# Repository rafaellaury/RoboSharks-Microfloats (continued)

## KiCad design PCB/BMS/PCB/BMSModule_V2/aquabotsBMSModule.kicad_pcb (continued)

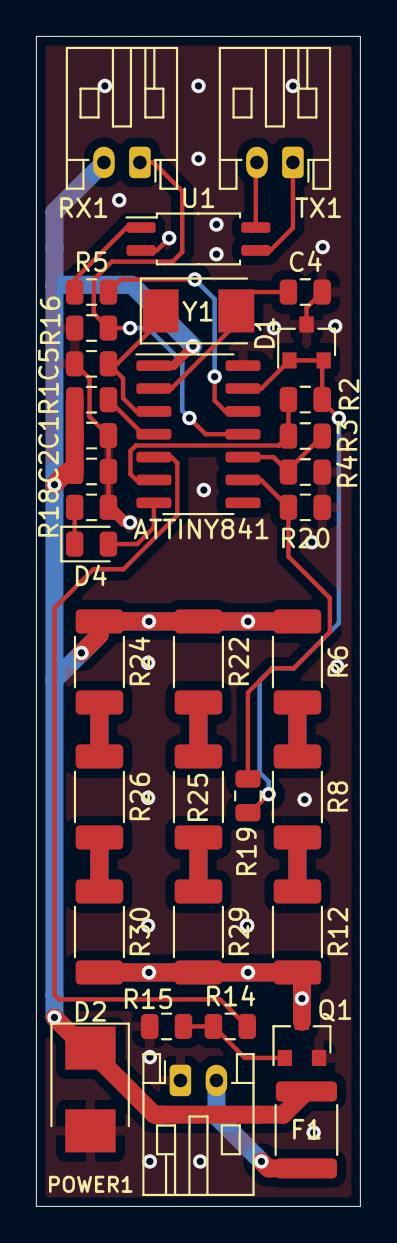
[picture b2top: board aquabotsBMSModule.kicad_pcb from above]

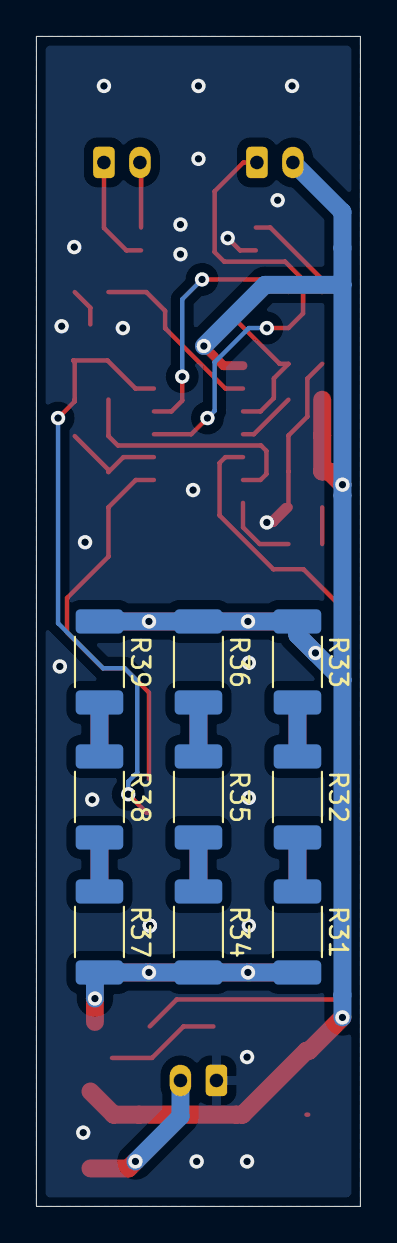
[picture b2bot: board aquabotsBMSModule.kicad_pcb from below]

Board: 2 copper layers, 18.0 x 65.0 mm, 44 parts (9 on the bottom side), 32 nets.

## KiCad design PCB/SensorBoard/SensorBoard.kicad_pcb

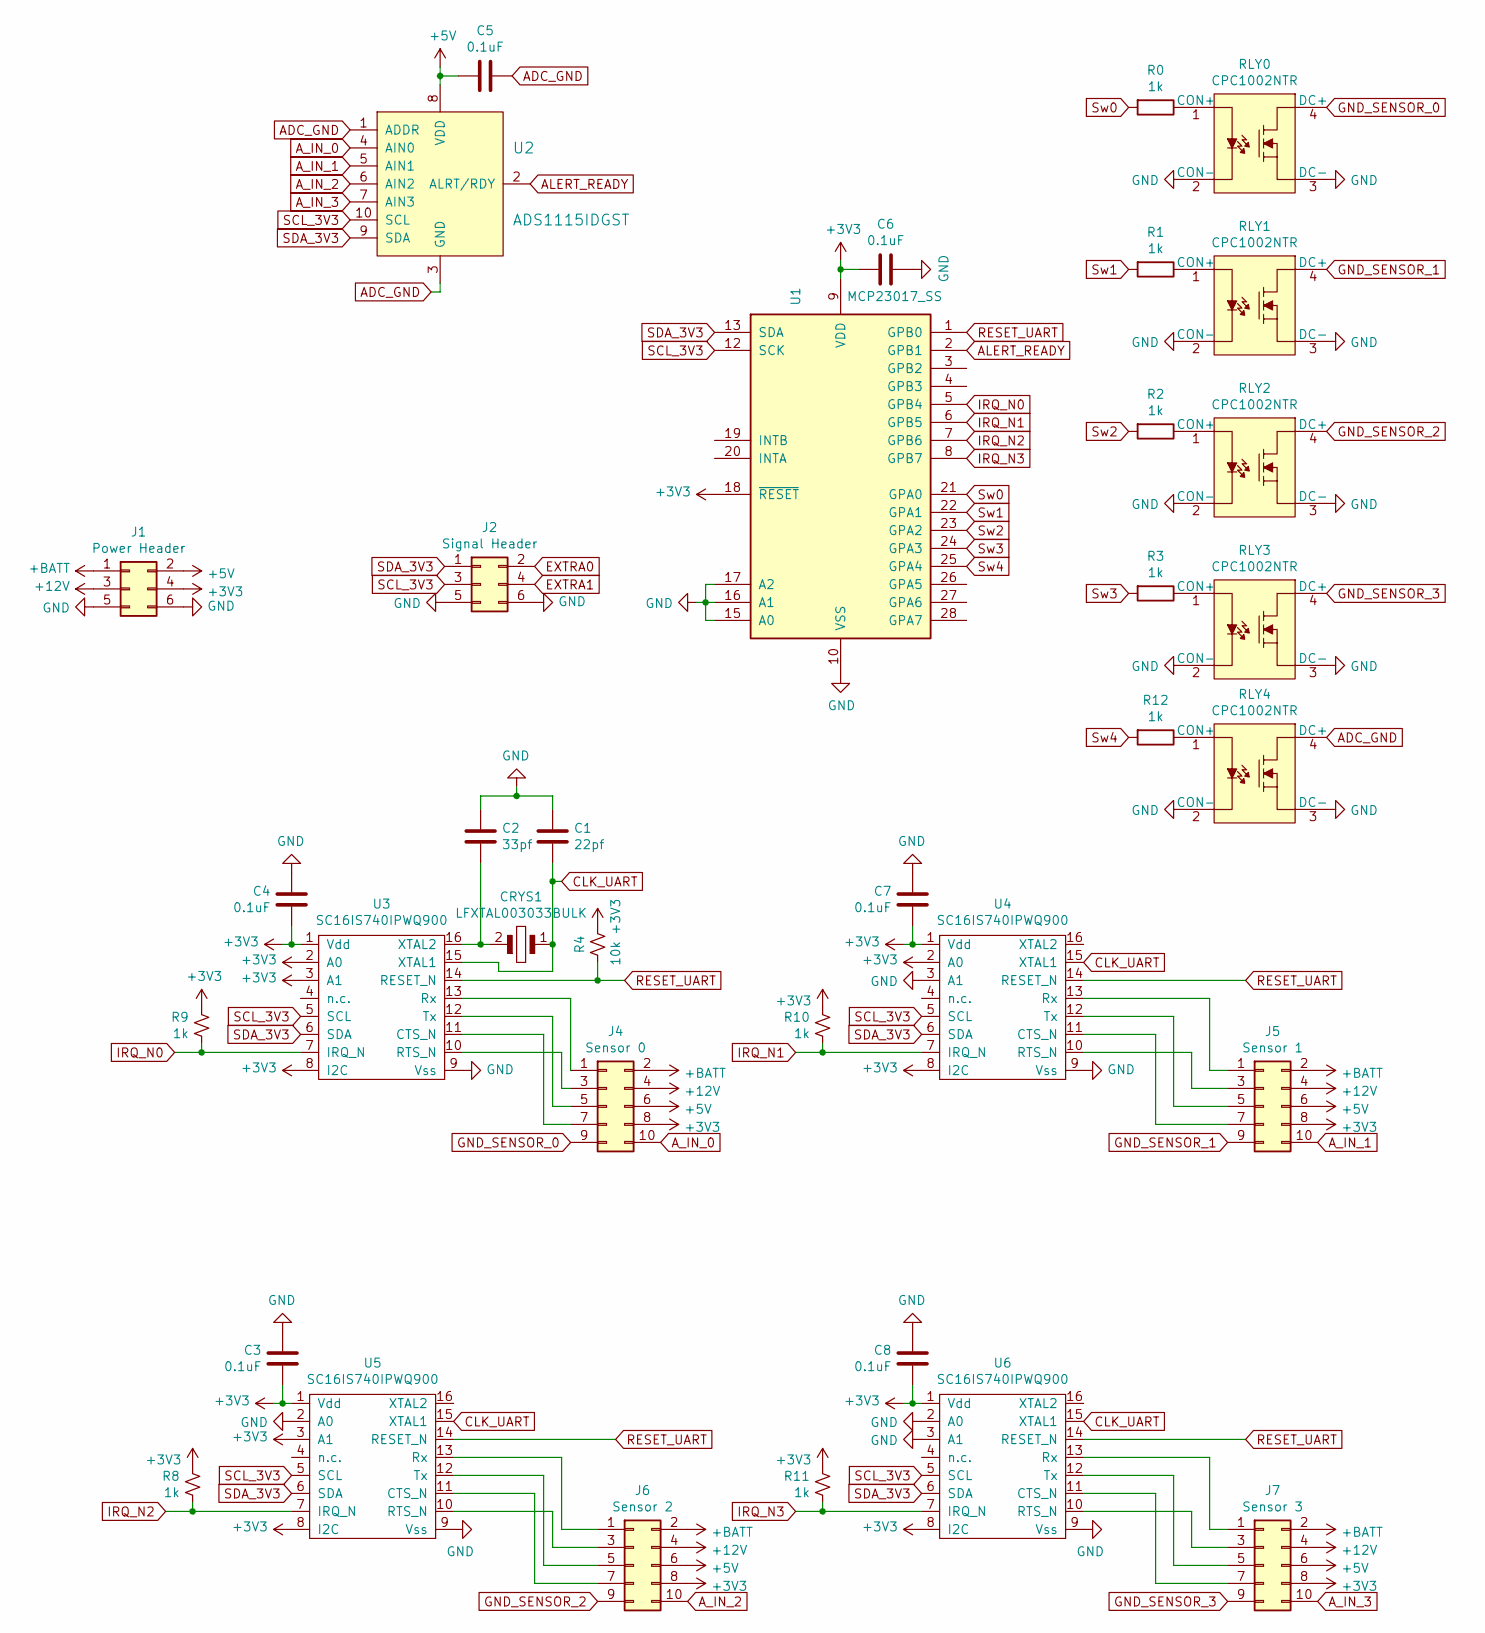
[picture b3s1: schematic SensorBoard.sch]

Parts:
C1: 22pf; C_0603_1608Metric_Pad1.05x0.95mm_HandSolder
C2: 33pf; C_0603_1608Metric_Pad1.05x0.95mm_HandSolder
C3, C4, C5, C6, C7, C8: 0.1uF; C_0603_1608Metric_Pad1.05x0.95mm_HandSolder
CRYS1: LFXTAL003033BULK; Crystal_HC49-U_Vertical
J1: Power Header; PinHeader_2x03_P2.54mm_Vertical
J2: Signal Header; PinHeader_2x03_P2.54mm_Vertical
J4: Sensor 0; Molex_Nano-Fit_105314-xx10_2x05_P2.50mm_Horizontal
J5: Sensor 1; Molex_Nano-Fit_105314-xx10_2x05_P2.50mm_Horizontal
J6: Sensor 2; Molex_Nano-Fit_105314-xx10_2x05_P2.50mm_Horizontal
J7: Sensor 3; Molex_Nano-Fit_105314-xx10_2x05_P2.50mm_Horizontal
R0, R1, R2, R3, R8, R9, R10, R11, R12: 1k; R_0805_2012Metric_Pad1.15x1.40mm_HandSolder
R4: 10k; R_0805_2012Metric_Pad1.15x1.40mm_HandSolder
RLY0, RLY1, RLY2, RLY3, RLY4: CPC1002NTR; SOP-4_3.8x4.1mm_P2.54mm; MPN CPC1002NTR; Digi-Key_PN CLA230CT-ND
U1: MCP23017_SS; SSOP-28_5.3x10.2mm_P0.65mm
U2: ADS1115IDGST; VSSOP-10_3x3mm_P0.5mm; MPN ADS1115IDGST; Digi-Key_PN 296-24934-1-ND
U3, U4, U5, U6: SC16IS740IPWQ900; TSSOP-16_4.4x5mm_P0.65mm

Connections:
+3V3: C3.2, C4.2, C6.2, C7.2, C8.2, J1.4, J4.8, J5.8, J6.8, J7.8, R4.2, R8.2, R9.2, R10.2, R11.2, U1.9 (VDD), U1.18 (~RESET~), U3.1 (Vdd), U3.2 (A0), U3.3 (A1), U3.8 (I2C), U4.1 (Vdd), U4.2 (A0), U4.8 (I2C), U5.1 (Vdd), U5.3 (A1), U5.8 (I2C), U6.1 (Vdd), U6.8 (I2C)
+5V: C5.2, J1.2, J4.6, J5.6, J6.6, J7.6, U2.8 (VDD)
+12V: J1.3, J4.4, J5.4, J6.4, J7.4
+BATT: J1.1, J4.2, J5.2, J6.2, J7.2
ADC_GND: C5.1, RLY4.4 (DC+), U2.1 (ADDR), U2.3 (GND)
ALERT_READY: U1.2 (GPB1), U2.2 (ALRT/RDY)
A_IN_0: J4.10, U2.4 (AIN0)
A_IN_1: J5.10, U2.5 (AIN1)
A_IN_2: J6.10, U2.6 (AIN2)
A_IN_3: J7.10, U2.7 (AIN3)
CLK_UART: C1.2, CRYS1.1, U3.15 (XTAL1), U4.15 (XTAL1), U5.15 (XTAL1), U6.15 (XTAL1)
EXTRA0: J2.2
EXTRA1: J2.4
GND: C1.1, C2.1, C3.1, C4.1, C6.1, C7.1, C8.1, J1.5, J1.6, J2.5, J2.6, RLY0.2 (CON-), RLY0.3 (DC-), RLY1.2 (CON-), RLY1.3 (DC-), RLY2.2 (CON-), RLY2.3 (DC-), RLY3.2 (CON-), RLY3.3 (DC-), RLY4.2 (CON-), RLY4.3 (DC-), U1.10 (VSS), U1.15 (A0), U1.16 (A1), U1.17 (A2), U3.9 (Vss), U4.3 (A1), U4.9 (Vss), U5.2 (A0), U5.9 (Vss), U6.2 (A0), U6.3 (A1), U6.9 (Vss)
GND_SENSOR_0: J4.9, RLY0.4 (DC+)
GND_SENSOR_1: J5.9, RLY1.4 (DC+)
GND_SENSOR_2: J6.9, RLY2.4 (DC+)
GND_SENSOR_3: J7.9, RLY3.4 (DC+)
IRQ_N0: R9.1, U1.5 (GPB4), U3.7 (IRQ_N)
IRQ_N1: R10.1, U1.6 (GPB5), U4.7 (IRQ_N)
IRQ_N2: R8.1, U1.7 (GPB6), U5.7 (IRQ_N)
IRQ_N3: R11.1, U1.8 (GPB7), U6.7 (IRQ_N)
unnamed: C2.2, CRYS1.2, U3.16 (XTAL2)
unnamed: J4.1, U3.13 (Rx)
unnamed: J4.3, U3.10 (RTS_N)
unnamed: J4.5, U3.12 (Tx)
unnamed: J4.7, U3.11 (CTS_N)
unnamed: J5.1, U4.13 (Rx)
unnamed: J5.3, U4.10 (RTS_N)
unnamed: J5.5, U4.12 (Tx)
unnamed: J5.7, U4.11 (CTS_N)
unnamed: J6.1, U5.13 (Rx)
unnamed: J6.3, U5.10 (RTS_N)
unnamed: J6.5, U5.12 (Tx)
unnamed: J6.7, U5.11 (CTS_N)
unnamed: J7.1, U6.13 (Rx)
unnamed: J7.3, U6.10 (RTS_N)
unnamed: J7.5, U6.12 (Tx)
unnamed: J7.7, U6.11 (CTS_N)
unnamed: R0.1, RLY0.1 (CON+)
unnamed: R1.1, RLY1.1 (CON+)
unnamed: R2.1, RLY2.1 (CON+)
unnamed: R3.1, RLY3.1 (CON+)
unnamed: R12.1, RLY4.1 (CON+)
RESET_UART: R4.1, U1.1 (GPB0), U3.14 (RESET_N), U4.14 (RESET_N), U5.14 (RESET_N), U6.14 (RESET_N)
SCL_3V3: J2.3, U1.12 (SCK), U2.10 (SCL), U3.5 (SCL), U4.5 (SCL), U5.5 (SCL), U6.5 (SCL)
SDA_3V3: J2.1, U1.13 (SDA), U2.9 (SDA), U3.6 (SDA), U4.6 (SDA), U5.6 (SDA), U6.6 (SDA)
Sw0: R0.2, U1.21 (GPA0)
Sw1: R1.2, U1.22 (GPA1)
Sw2: R2.2, U1.23 (GPA2)
Sw3: R3.2, U1.24 (GPA3)
Sw4: R12.2, U1.25 (GPA4)

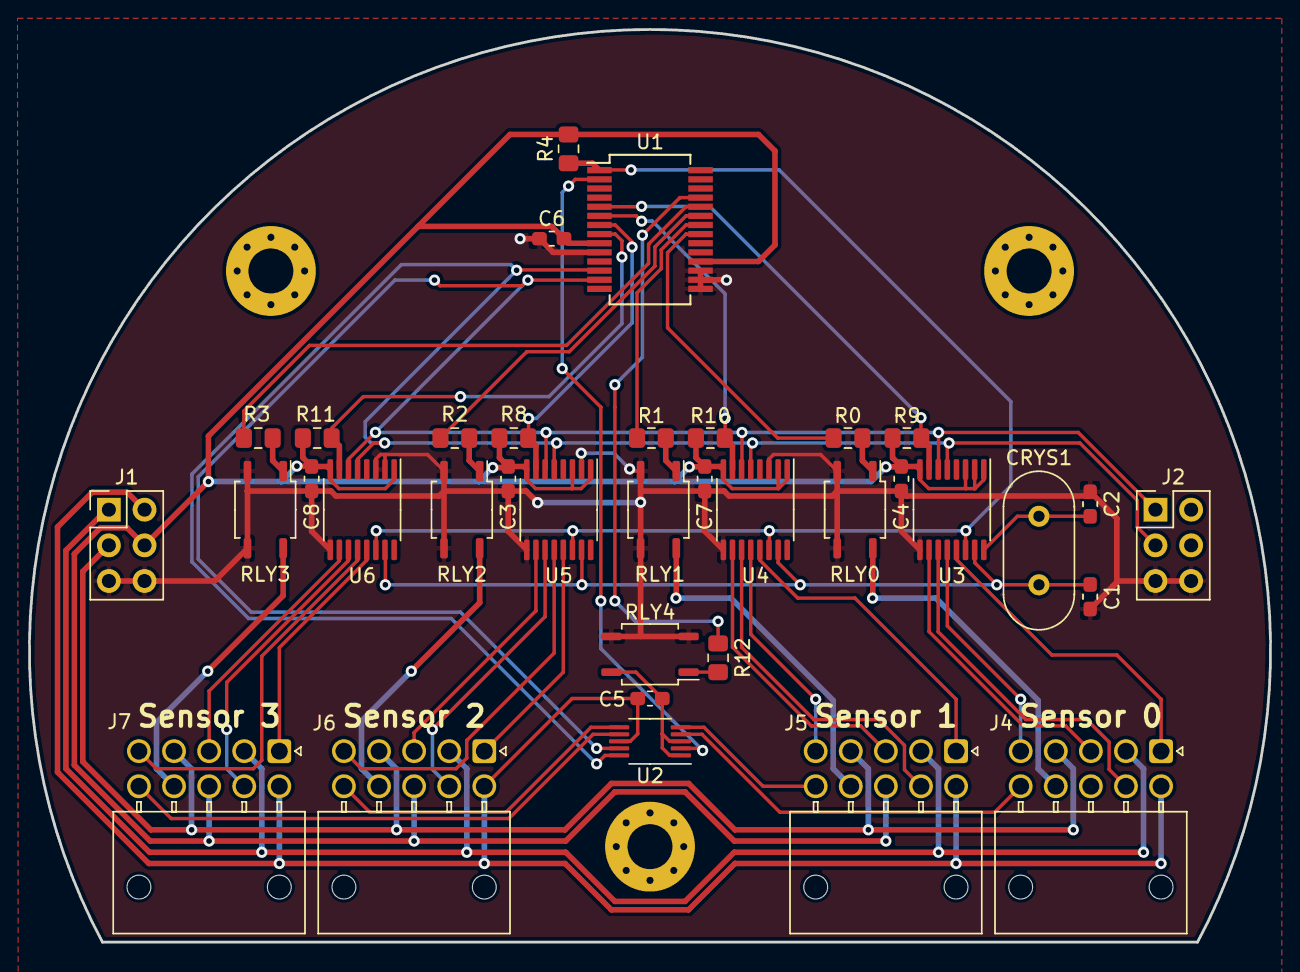
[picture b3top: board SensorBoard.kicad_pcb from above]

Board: 2 copper layers, 88.4 x 65.0 mm, 36 parts (0 on the bottom side), 50 nets.

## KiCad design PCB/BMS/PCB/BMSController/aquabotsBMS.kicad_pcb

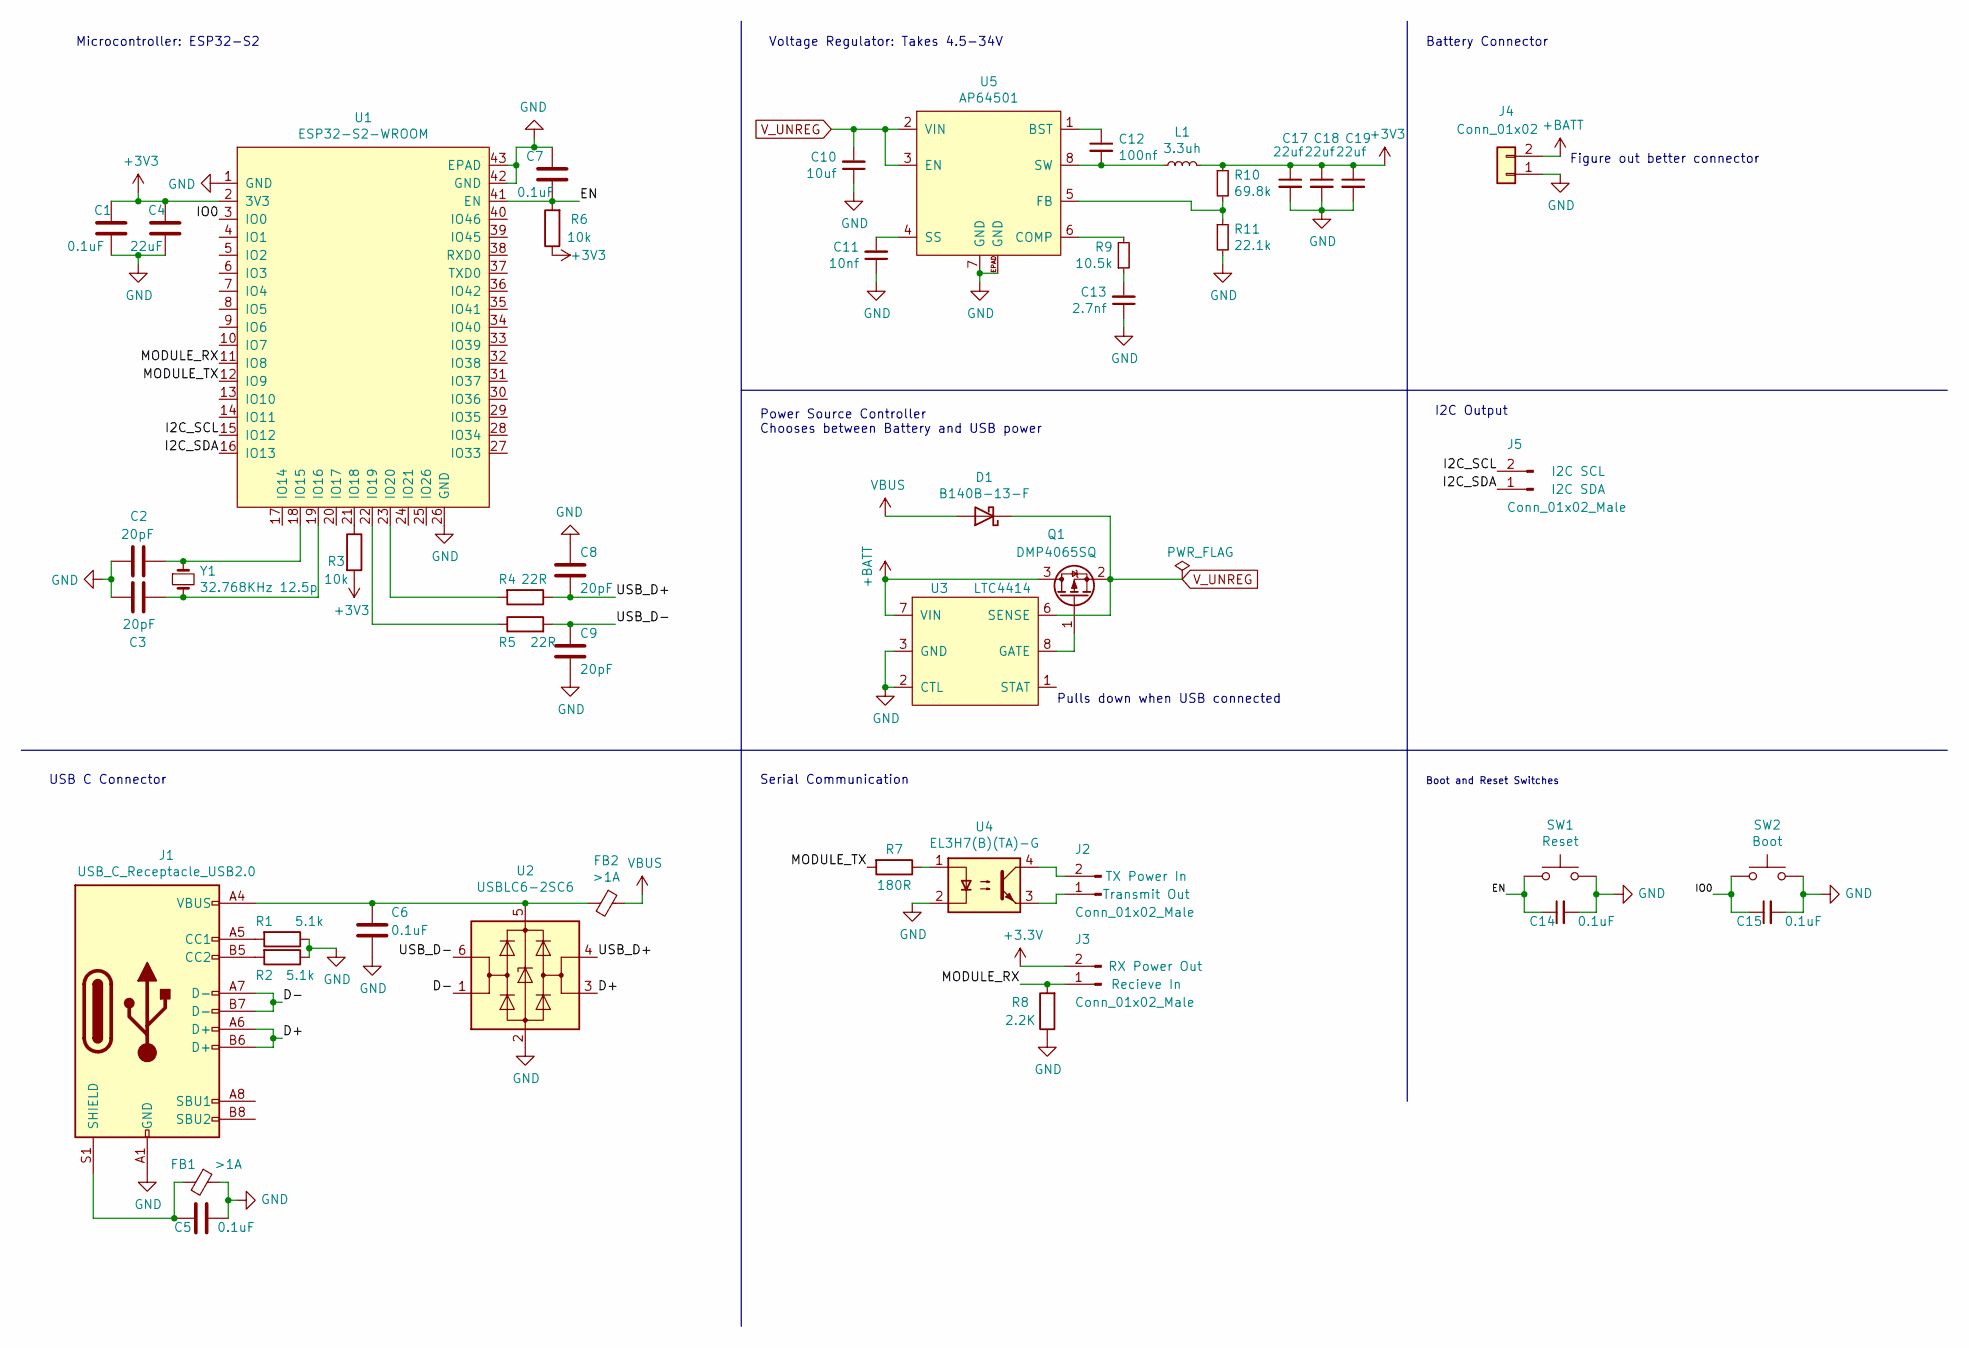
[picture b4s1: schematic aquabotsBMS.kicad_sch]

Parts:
C1, C5, C6, C7, C14, C15: 0.1uF; C_0603_1608Metric
C2, C3, C8, C9: 20pF; C_0603_1608Metric
C4: 22uF; C_0603_1608Metric
C10: 10uf; C_1206_3216Metric
C11: 10nf; C_0603_1608Metric
C12: 100nf; C_0603_1608Metric
C13: 2.7nf; C_0603_1608Metric
C17, C18, C19: 22uf; C_1206_3216Metric
D1: B140B-13-F; D_SMA
FB1, FB2: >1A; L_0603_1608Metric
J1: USB_C_Receptacle_USB2.0; USB_C_Receptacle_HRO_TYPE-C-31-M-12
J2, J3, J5: Conn_01x02_Male; JST_PH_S2B-PH-K_1x02_P2.00mm_Horizontal
J4: Conn_01x02; PinHeader_1x02_P2.54mm_Vertical
L1: 3.3uh; L_Wuerth_HCI-1050
Q1: DMP4065SQ; SOT-23
R1, R2: 5.1k; R_0603_1608Metric
R3, R6: 10k; R_0603_1608Metric
R4, R5: 22R; R_0603_1608Metric
R7: 180R; R_0603_1608Metric
R8: 2.2K; R_0603_1608Metric; LCSCStockCode C17520
R9: 10.5k; R_0603_1608Metric
R10: 69.8k; R_0603_1608Metric
R11: 22.1k; R_0603_1608Metric
SW1: Reset; SW_Push_SPST_NO_Alps_SKRK
SW2: Boot; SW_Push_SPST_NO_Alps_SKRK
U1: ESP32-S2-WROOM
U2: USBLC6-2SC6; SOT-23-6
U3: LTC4414; MSOP-8_3x3mm_P0.65mm
U4: EL3H7(B)(TA)-G; SOP-4_4.4x2.6mm_P1.27mm; LCSCStockCode C32565
U5: AP64501; AP64501SP-13
Y1: 32.768KHz 12.5p; Crystal_SMD_3215-2Pin_3.2x1.5mm

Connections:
+BATT: J4.2, Q1.3 (D), U3.7 (VIN)
/D+: J1.A6 (D+), J1.B6 (D+), U2.3 (I/O2)
/D-: J1.A7 (D-), J1.B7 (D-), U2.1 (I/O1)
/EN: C7.2, C14.1, R6.2, SW1.1, U1.41 (EN)
/I2C_SCL: J5.2, U1.15 (IO12)
/I2C_SDA: J5.1, U1.16 (IO13)
/IO0: C15.1, SW2.1, U1.3 (IO0)
/MODULE_RX: J3.1, R8.2, U1.11 (IO8)
/MODULE_TX: R7.2, U1.12 (IO9)
/USB_D+: C8.2, R4.1, U2.4 (I/O2)
/USB_D-: C9.1, R5.2, U2.6 (I/O1)
GND: C1.2, C2.2, C3.1, C4.2, C5.2, C6.2, C7.1, C8.1, C9.2, C10.1, C11.1, C13.1, C14.2, C15.2, C17.2, C18.2, C19.2, FB1.1, J1.A1 (GND), J1.A12 (GND), J1.B1 (GND), J1.B12 (GND), J4.1, R1.1, R2.1, R8.1, R11.2, SW1.2, SW2.2, U1.1 (GND), U1.26 (GND), U1.42 (GND), U1.43 (EPAD), U2.2 (GND), U3.2 (CTL), U3.3 (GND), U4.2, U5.7 (GND), U5.EPAD (GND)
unnamed: C2.1, U1.18 (IO15), Y1.1
unnamed: C3.2, U1.19 (IO16), Y1.2
unnamed: C5.1, FB1.2, J1.S1 (SHIELD)
unnamed: C6.1, FB2.2, J1.A4 (VBUS), J1.A9 (VBUS), J1.B4 (VBUS), J1.B9 (VBUS), U2.5 (VBUS)
unnamed: C11.2, U5.4 (SS)
unnamed: C12.1, U5.1 (BST)
unnamed: C12.2, L1.1, U5.8 (SW)
unnamed: C13.2, R9.1
unnamed: J1.A5 (CC1), R1.2
unnamed: J1.B5 (CC2), R2.2
unnamed: J2.1, U4.3
unnamed: J2.2, U4.4
unnamed: Q1.1 (G), U3.8 (GATE)
unnamed: R3.1, U1.21 (IO18)
unnamed: R4.2, U1.23 (IO20)
unnamed: R5.1, U1.22 (IO19)
unnamed: R7.1, U4.1
unnamed: R9.2, U5.6 (COMP)
unnamed: R10.2, R11.1, U5.5 (FB)
VBUS: D1.2 (A), FB2.1
V_UNREG: C10.2, D1.1 (K), Q1.2 (S), U3.6 (SENSE), U5.2 (VIN), U5.3 (EN)

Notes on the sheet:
Figure out better connector
I2C Output
Pulls down when USB connected
Serial Communication
Microcontroller: ESP32-S2
Power Source Controller Chooses between Battery and USB power
Voltage Regulator: Takes 4.5-34V
Battery Connector
Boot and Reset Switches
USB C Connector

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
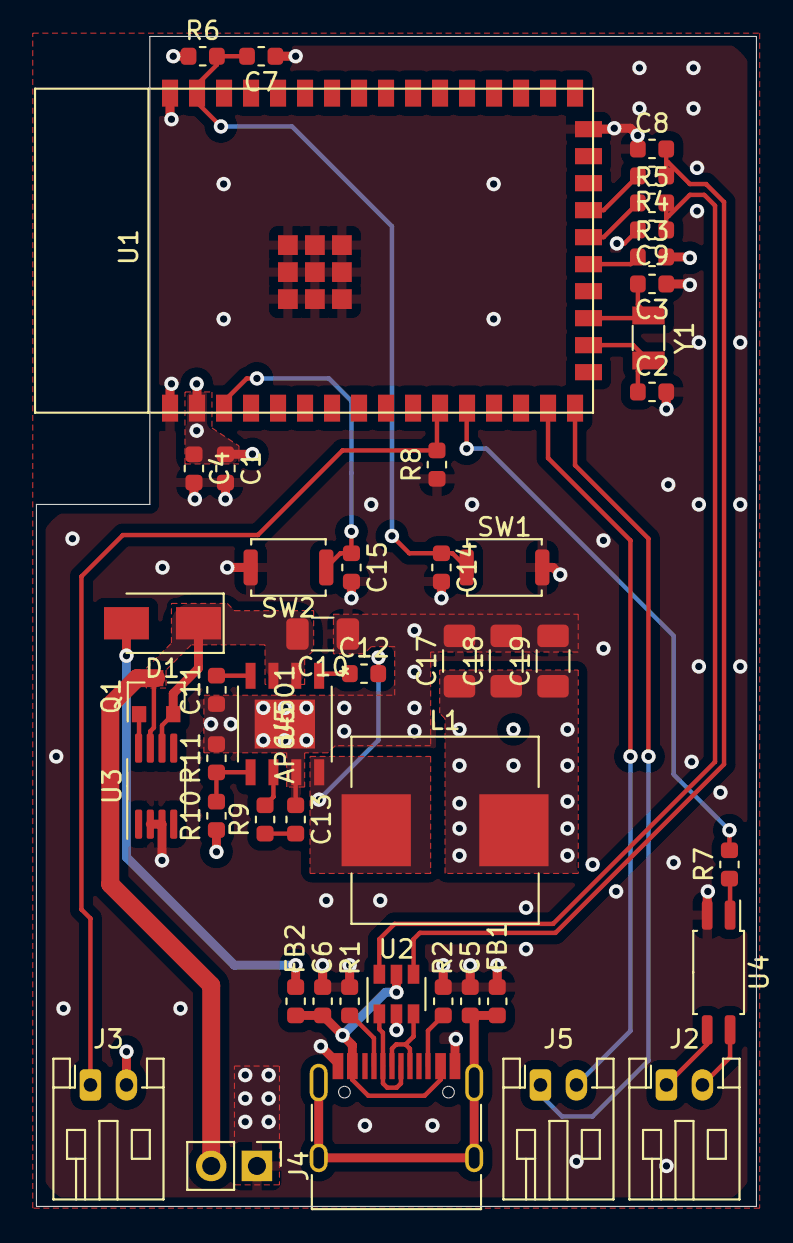
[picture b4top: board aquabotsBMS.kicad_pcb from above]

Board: 4 copper layers, 40.0 x 65.0 mm, 47 parts (0 on the bottom side), 34 nets.

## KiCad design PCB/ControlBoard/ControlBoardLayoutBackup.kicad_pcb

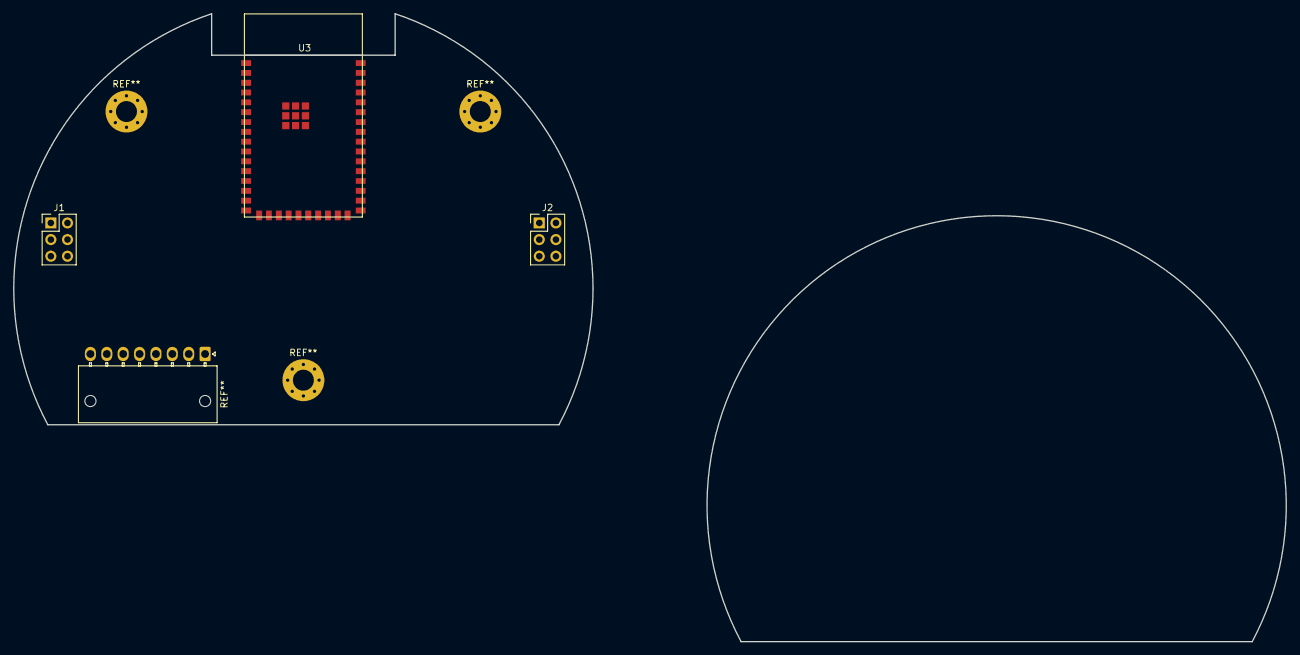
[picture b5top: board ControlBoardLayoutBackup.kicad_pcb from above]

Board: 2 copper layers, 88.4 x 62.7 mm, 3 parts (0 on the bottom side), 2 nets, no tracks yet.

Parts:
J1: Power Header; PinHeader_2x03_P2.54mm_Vertical
J2: Signal Header; PinHeader_2x03_P2.54mm_Vertical
U3: ESP32-S2-WROOM

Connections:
+3V3: J1.4, U3.2
GND: J1.5, J1.6, J2.5, J2.6, U3.1, U3.26, U3.42, U3.43

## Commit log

2022-03-06 Setting up the repository
    Merging files from the VIP Team's Lagrangian Profiler github (https://github.gatech.edu/Aquabots-VIP/LagrangianProfiler) into the RoboSharks repository.
2022-03-06 BMS Module PCB Gerber and BOM files
    Generated Gerber and BOM files for the BMS Module PCB.
2022-03-06 Restructuring the Repository
    Added CAD Design folder and bundled all miscellaneous
2022-03-07 BMS Controller Update
    Edited the board and created Gerber files.
2022-03-10 Updated with new BMS Module PCB
    Fixed footprints on some of the components based on the replacements we selected when ordering parts. Nothing else was changed from the previous version except those footprints
2022-03-10 Deleted a previous unfinished version
    Deleted a previous version that was unfinished and was not the one we printed out. This will help to limit confusion for which PCB layout we chose
2022-03-11 Sensor Board File Update to Kicad 6
    Here we go
2022-03-14 MicroFloat Test Code Upload & BMS Controller PCB
    Copied RUR Arduino test code into our repository for easy access. Also created drill files and a new gerber ZIP for the BMS Controller PCB.
2022-03-14 Control Board issues file added
2022-03-15 Updates to Kicad V6.0
    It updated from old format to the new format of Kicad
2022-03-15 First Control Board Update
    Added a cutout for the USB-C header.
2022-03-20 Control Board Update #1
    Title
2022-03-22 Control Board Updates
    Made most of the changes suggested in "control board issues.txt", sent off an email to Matthew with some suggestions and questions. Will complete design and then start speccing parts after that.
2022-03-28 New Updates
    Created an I2C and SPI data bus. Routed all the corrections according to Matthew Woodward in the schematic. Still working on finishing the routing in the PCB editor.
2022-03-31 Update ControlBoard.kicad_pcb
    Latest changes to the routing for version 2
2022-04-01 Final Control Board Updates
    Finished the PCB routing and went through the DRC and corrected most errors.
2022-04-01 Update to Version 2
    Updated to add jumpers for the antenna switch on the LoRa. One is Vcc and the other is GND. Will need to test and solder once correct layout is found.
2022-04-13 Minor control board updates
    Lingering updates that hadn't been pushed, moved some silkscreen around, couple other miscellaneous updates.
2022-04-13 Uploading Sensor Board Testing Code (Rough)
    Will need to be touched up later, this is just the first draft of all the Sensor Board testing code that was used today. Includes code for the MBED side as well as the Arduino side.
2022-04-27 New Matlab Simulations Folder
    Updated with my code for our Power Analysis and Antenna Simulations. Power is a rough estimation. I believe the current for the motor might be an overestimation but depends on the new control board.
2022-05-03 Adding CAD files from this semester
    CAD files from all of our current models and previous models we used are uploaded. Most are in internal files based on the subsystems.
2022-05-03 Update README.md
    Updated the README for CAD models.
2022-05-03 Adding CAD image
2022-05-03 Added README documentation
    I'll see you at the beginning, friend.
2022-05-03 Adding logo for doco
    Save the world then we'll balance the books.
2022-05-03 Prettyfied
    In a world where youre pretending to be a millionaire, Brooks Brothers won't cut it.
